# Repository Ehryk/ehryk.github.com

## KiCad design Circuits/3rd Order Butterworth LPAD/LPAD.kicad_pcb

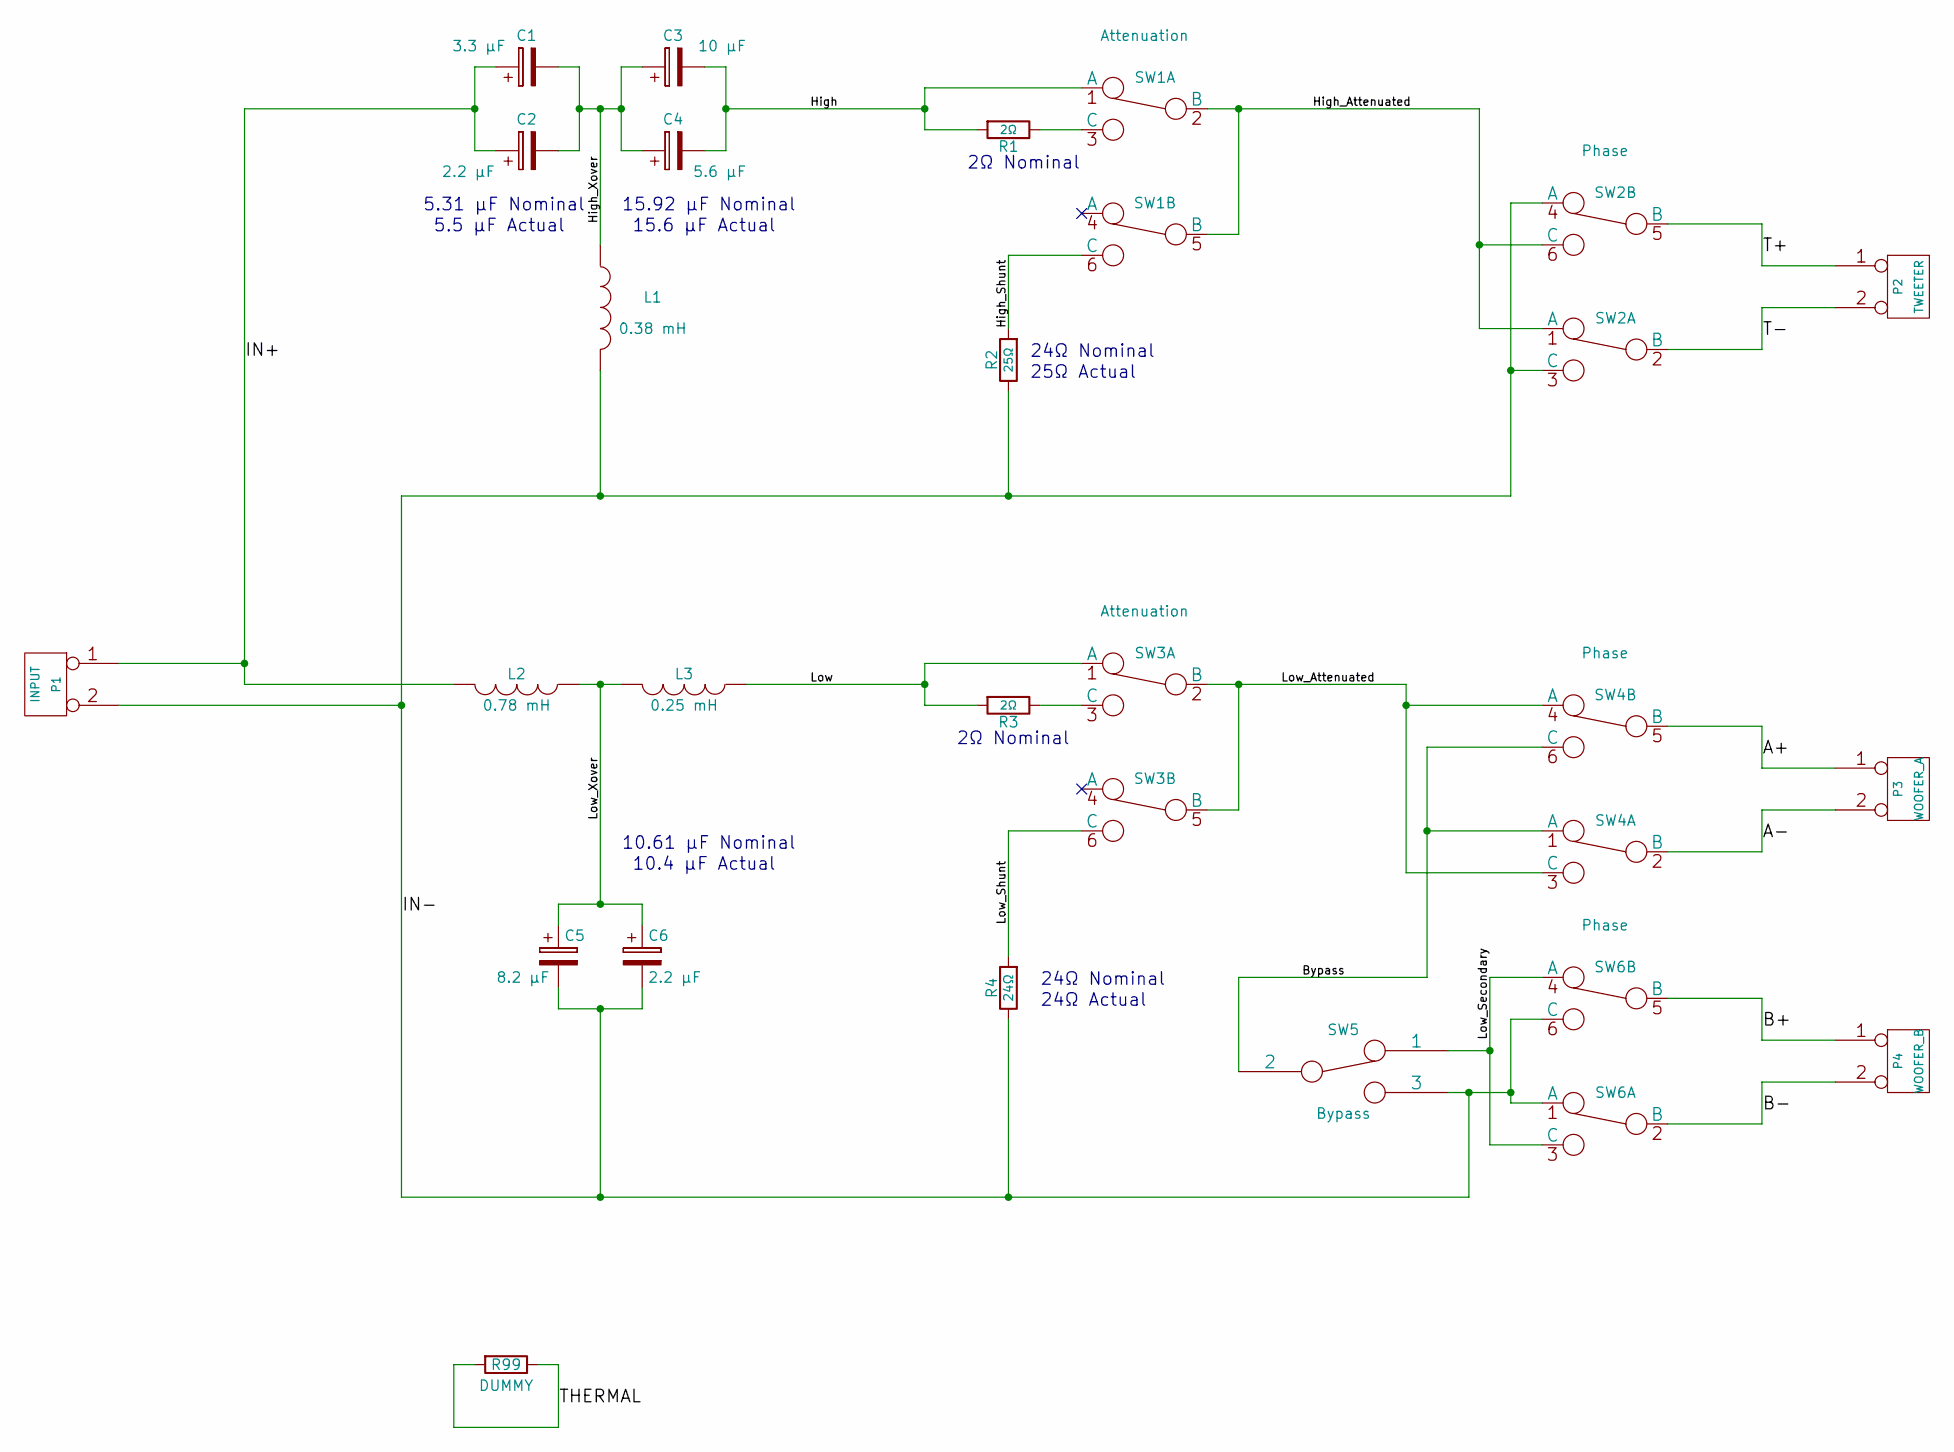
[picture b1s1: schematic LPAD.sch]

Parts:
C1: 3.3 μF; C_AXIAL_15x36
C2, C6: 2.2 μF; C_AXIAL_15x24
C3: 10 μF; C_AXIAL_25x36
C4: 5.6 μF; C_AXIAL_19x36
C5: 8.2 μF; C_AXIAL_23x36
L1: 0.38 mH; ED110-2
L2: 0.78 mH; ED110-2
L3: 0.25 mH; ED110-2
P1: INPUT; ED110-2
P2: TWEETER; ED110-2
P3: WOOFER_A; ED110-2
P4: WOOFER_B; ED110-2
R1: 2Ω; R_WIREWOUND_25W
R2: 25Ω; R_WIREWOUND_25W
R3: 2Ω; R_WIREWOUND_100W
R4: 24Ω; R_WIREWOUND_100W
R99: DUMMY
SW1, SW3: Attenuation; SW_DPDT_RED
SW2, SW4, SW6: Phase; SW_DPDT_RED
SW5: Bypass; SW_SPDT_RED

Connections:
/A+: P3.1, SW4.5 (B)
/A-: P3.2 (PM), SW4.2 (B)
/B+: P4.1, SW6.5 (B)
/B-: P4.2 (PM), SW6.2 (B)
/Bypass: SW4.1 (A), SW4.6 (C), SW5.2
/High: C3.2, C4.2, R1.2, SW1.1 (A)
/High_Attenuated: SW1.2 (B), SW1.5 (B), SW2.1 (A), SW2.6 (C)
/High_Shunt: R2.2, SW1.6 (C)
/High_Xover: C1.2, C2.2, C3.1, C4.1, L1.1
/IN+: C1.1, C2.1, L2.2, P1.1
/IN-: C5.2, C6.2, L1.2, P1.2 (PM), R2.1, R4.1, SW2.3 (C), SW2.4 (A), SW5.3, SW6.1 (A), SW6.6 (C)
/Low: L3.1, R3.2, SW3.1 (A)
/Low_Attenuated: SW3.2 (B), SW3.5 (B), SW4.3 (C), SW4.4 (A)
/Low_Secondary: SW5.1, SW6.3 (C), SW6.4 (A)
/Low_Shunt: R4.2, SW3.6 (C)
/Low_Xover: C5.1, C6.1, L2.1, L3.2
/T+: P2.1, SW2.5 (B)
/T-: P2.2 (PM), SW2.2 (B)
unnamed: R1.1, SW1.3 (C)
unnamed: R3.1, SW3.3 (C)
unnamed: R99.1, R99.2

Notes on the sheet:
10.61 μF Nominal
5.31 μF Nominal
15.92 μF Nominal
10.4 μF Actual
5.5 μF Actual
15.6 μF Actual
24Ω Nominal
24Ω Actual
25Ω Actual
2Ω Nominal

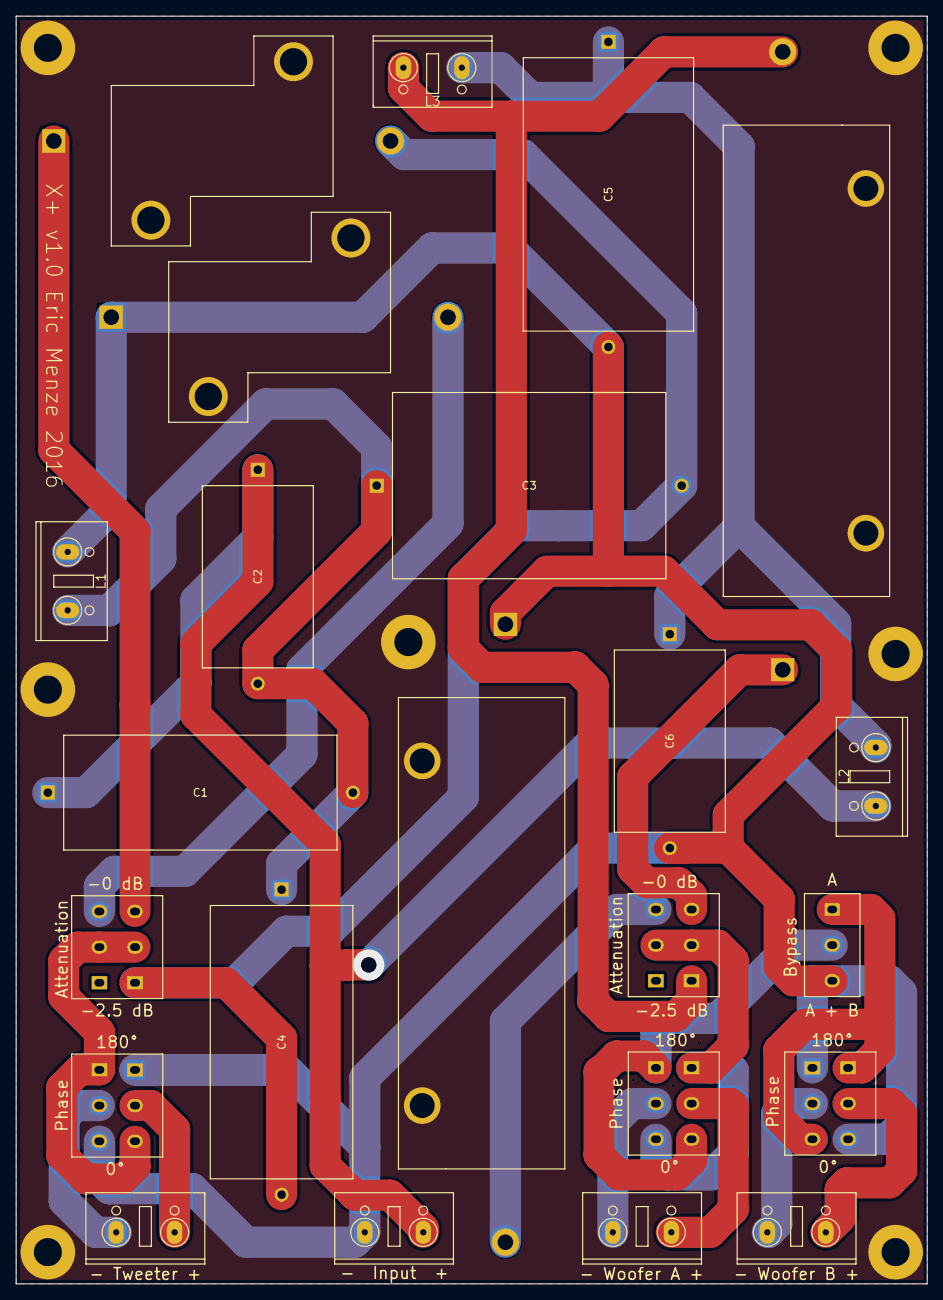
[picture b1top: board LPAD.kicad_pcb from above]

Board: 2 copper layers, 116.8 x 162.6 mm, 30 parts (0 on the bottom side), 20 nets.

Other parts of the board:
S1, S2, S3, S4, S5, S6, S7: #6; 6-32UNC_Screw_Hole

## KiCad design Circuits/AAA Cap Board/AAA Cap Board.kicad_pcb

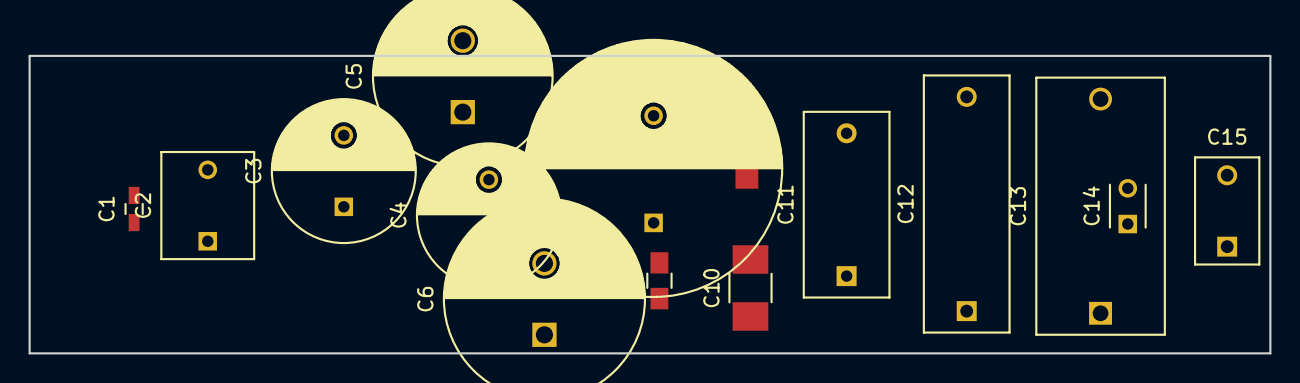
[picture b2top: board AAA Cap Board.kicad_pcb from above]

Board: 2 copper layers, 86.9 x 20.8 mm, 15 parts (0 on the bottom side), 2 nets, no tracks yet.

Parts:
C1: C; C_0603_HandSoldering
C2: CP; C_Rect_L7.5_W6.5_P5
C3: CP1; C_Radial_D10_L13_P5
C4: CP1; C_Radial_D10_L16_P5
C5: CP1; C_Radial_D12.5_L25_P5
C6: CP1; C_Radial_D14_L25_P5
C7: CP1; C_Radial_D18_L36_P7.5
C8: C; C_0805_HandSoldering
C9: C; C_1206_HandSoldering
C10: C; C_1210_HandSoldering
C11: CP; C_Rect_L13_W6_H12_P10
C12: CP; C_Rect_L18_W6_H12_P15
C13: CP; C_Rect_L18_W9_H15_P15
C14: C; C_Disc_D3_P2.5
C15: C; C_Disc_D7.5_P5

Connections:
unnamed: C1.1, C2.1, C3.1, C4.1, C5.1, C6.1, C7.1, C8.1, C9.1, C10.1, C11.1, C12.1, C13.1, C14.1, C15.1
unnamed: C1.2, C2.2, C3.2, C4.2, C5.2, C6.2, C7.2, C8.2, C9.2, C10.2, C11.2, C12.2, C13.2, C14.2, C15.2

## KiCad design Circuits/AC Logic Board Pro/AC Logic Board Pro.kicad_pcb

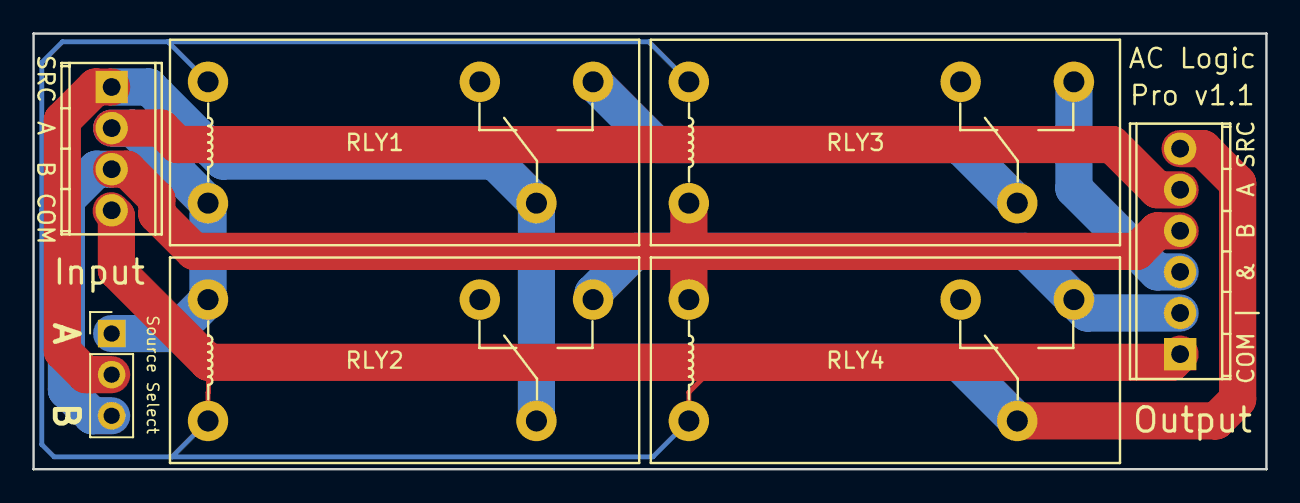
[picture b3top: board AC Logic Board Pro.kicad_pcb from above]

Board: 2 copper layers, 76.2 x 26.9 mm, 7 parts (0 on the bottom side), 7 nets.

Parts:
J1: Input; TerminalBlock_Phoenix_MPT-2.54mm_4pol
J2: Output; TerminalBlock_Phoenix_MPT-2.54mm_6pol
JP1: Source Select; Pin_Header_Straight_1x03_Pitch2.54mm
RLY1: AND_A; TE-RT1-3.5mm
RLY2: OR_A; TE-RT1-3.5mm
RLY3: AND_B; TE-RT1-3.5mm
RLY4: OR_B; TE-RT1-3.5mm

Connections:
A: J1.2, J2.5, JP1.1, RLY1.A2, RLY2.A1
AND: J2.3, RLY3.14
B: J1.3, J2.4, JP1.3, RLY3.A2, RLY4.A1
COMMON: J1.4, J2.1, RLY1.A1, RLY2.A2, RLY3.A1, RLY4.A2
INT_AND: RLY1.14, RLY3.11
OR: J2.2, RLY2.14, RLY4.14
SOURCE: J1.1, J2.6, JP1.2, RLY1.11, RLY2.11, RLY4.11

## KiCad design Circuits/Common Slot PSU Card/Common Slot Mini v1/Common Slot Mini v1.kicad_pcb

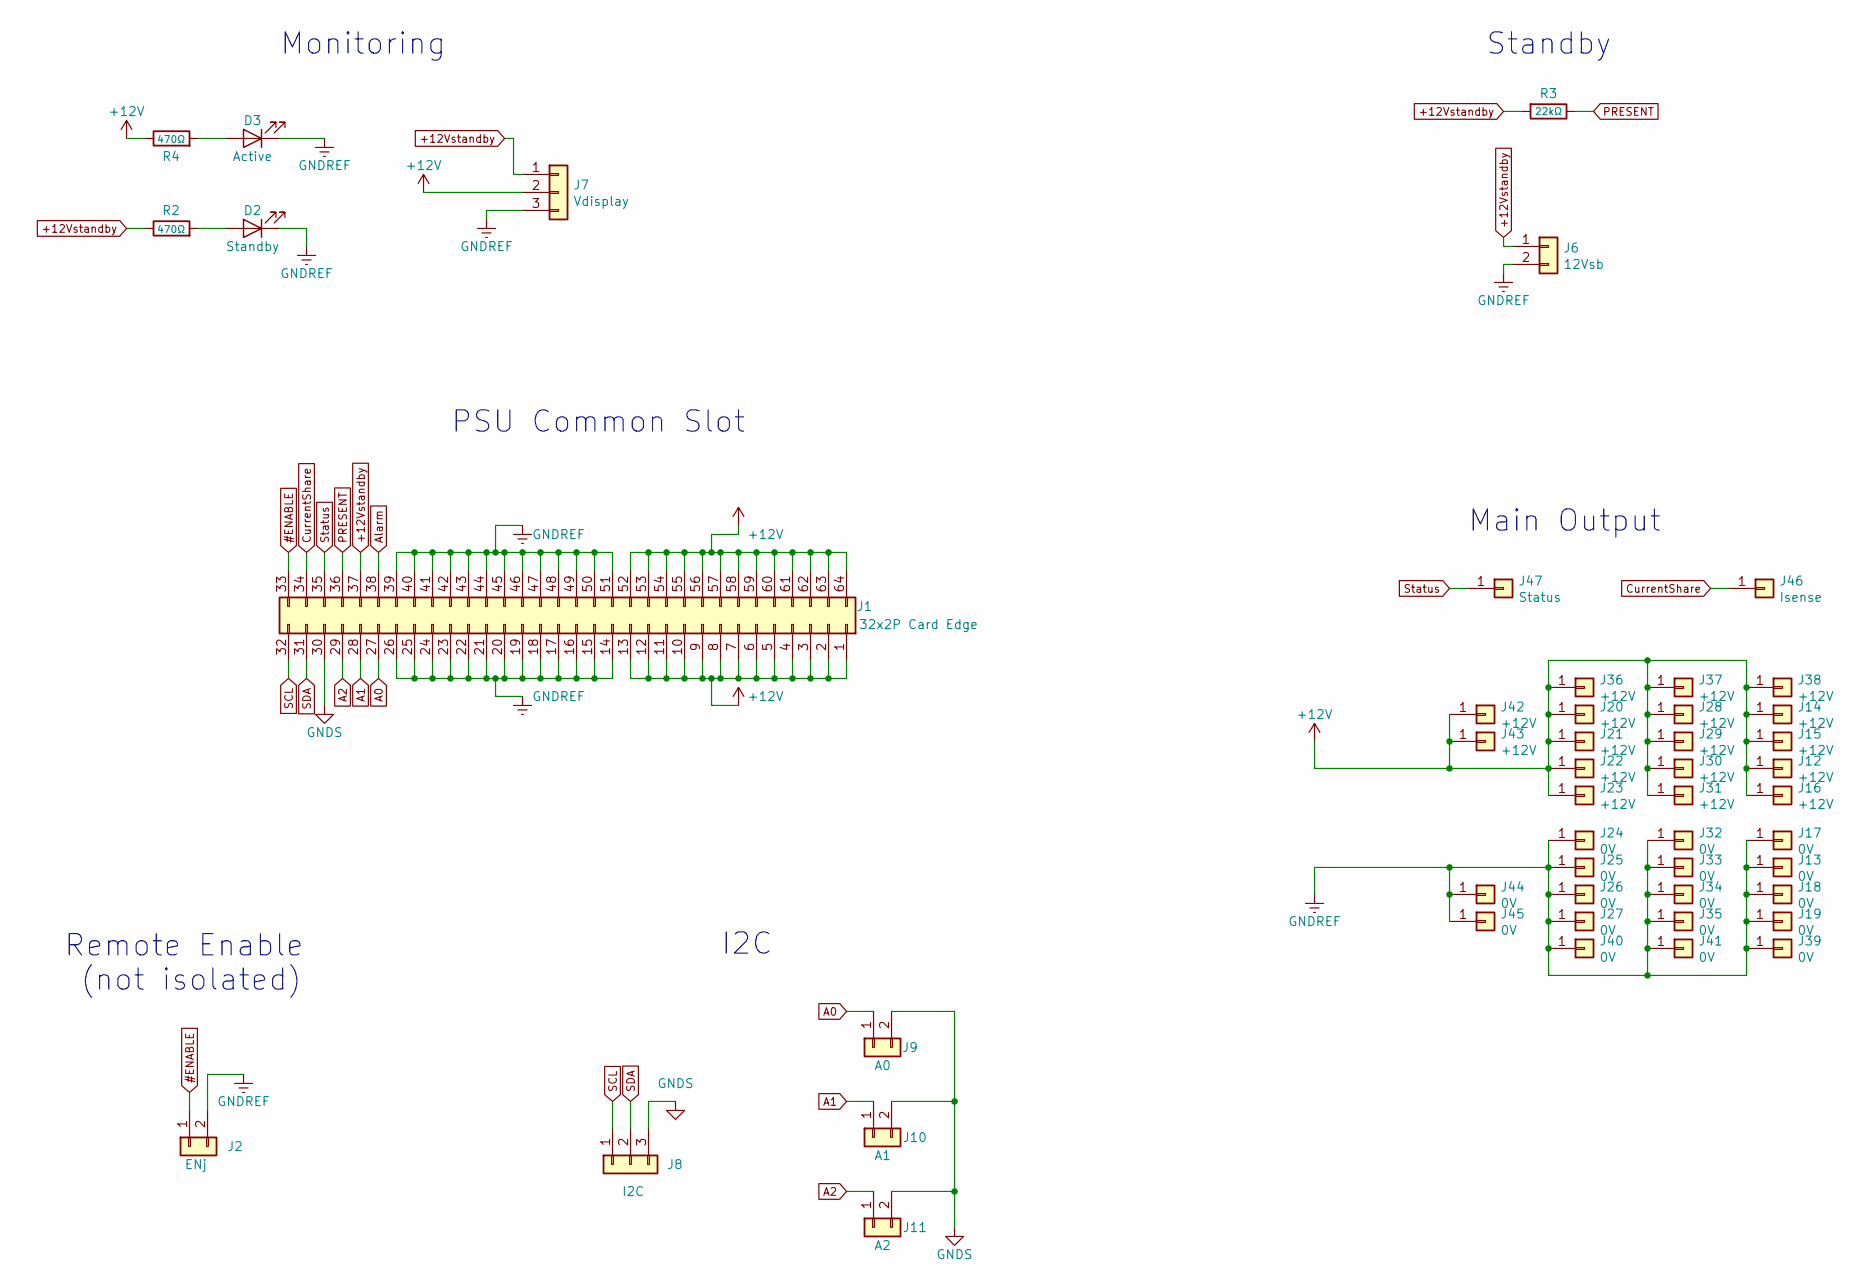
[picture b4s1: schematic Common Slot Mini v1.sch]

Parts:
D2: Standby; LED_1206_HandSoldering
D3: Active; LED_1206_HandSoldering
J1: 32x2P Card Edge; CommonSlot_2x32P_2.54mm
J2: ENj; Pin_Header_Straight_1x02_Pitch2.54mm
J6: 12Vsb; Pin_Header_Straight_1x02_Pitch2.54mm
J7: Vdisplay; Pin_Header_Straight_1x03_Pitch2.54mm
J8: I2C; PinHeader_1x03_P2.54mm_Vertical
J9: A0; SolderJumper-2_P1.3mm_Open_RoundedPad1.0x1.5mm
J10: A1; SolderJumper-2_P1.3mm_Open_RoundedPad1.0x1.5mm
J11: A2; SolderJumper-2_P1.3mm_Open_RoundedPad1.0x1.5mm
J12, J14, J15, J16, J20, J21, J22, J23, J28, J29, J30, J31, J36, J37, J38: +12V; WIRE-12AWG
J13, J17, J18, J19, J24, J25, J26, J27, J32, J33, J34, J35, J39, J40, J41: 0V; WIRE-12AWG
J42, J43: +12V; WIRE-16AWG
J44, J45: 0V; WIRE-16AWG
J46: Isense; WIRE-16AWG
J47: Status; WIRE-20AWG
R2, R4: 470Ω; R_1206_HandSoldering
R3: 22kΩ; R_1206_HandSoldering

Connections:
#ENABLE: J1.33, J2.1
+12V: J1.1, J1.2, J1.3, J1.4, J1.5, J1.6, J1.7, J1.8, J1.9, J1.10, J1.11, J1.12, J1.13, J1.52, J1.53, J1.54, J1.55, J1.56, J1.57, J1.58, J1.59, J1.60, J1.61, J1.62, J1.63, J1.64, J7.2, J12.1, J14.1, J15.1, J16.1, J20.1, J21.1, J22.1, J23.1, J28.1, J29.1, J30.1, J31.1, J36.1, J37.1, J38.1, J42.1, J43.1, R4.1
+12Vstandby: J1.37, J6.1, J7.1, R2.1, R3.2
A0: J1.27, J9.1
A1: J1.28, J10.1
A2: J1.29, J11.1
Alarm: J1.38
CurrentShare: J1.34, J46.1
GNDREF: D2.1 (K), D3.1 (K), J1.14, J1.15, J1.16, J1.17, J1.18, J1.19, J1.20, J1.21, J1.22, J1.23, J1.24, J1.25, J1.26, J1.39, J1.40, J1.41, J1.42, J1.43, J1.44, J1.45, J1.46, J1.47, J1.48, J1.49, J1.50, J1.51, J2.2, J6.2, J7.3, J13.1, J17.1, J18.1, J19.1, J24.1, J25.1, J26.1, J27.1, J32.1, J33.1, J34.1, J35.1, J39.1, J40.1, J41.1, J44.1, J45.1
GNDS: J1.30, J8.3, J9.2, J10.2, J11.2
unnamed: D2.2 (A), R2.2
unnamed: D3.2 (A), R4.2
PRESENT: J1.36, R3.1
SCL: J1.32, J8.1
SDA: J1.31, J8.2
Status: J1.35, J47.1

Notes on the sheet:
Remote Enable (not isolated)
Main Output
Standby
I2C
PSU Common Slot
Monitoring

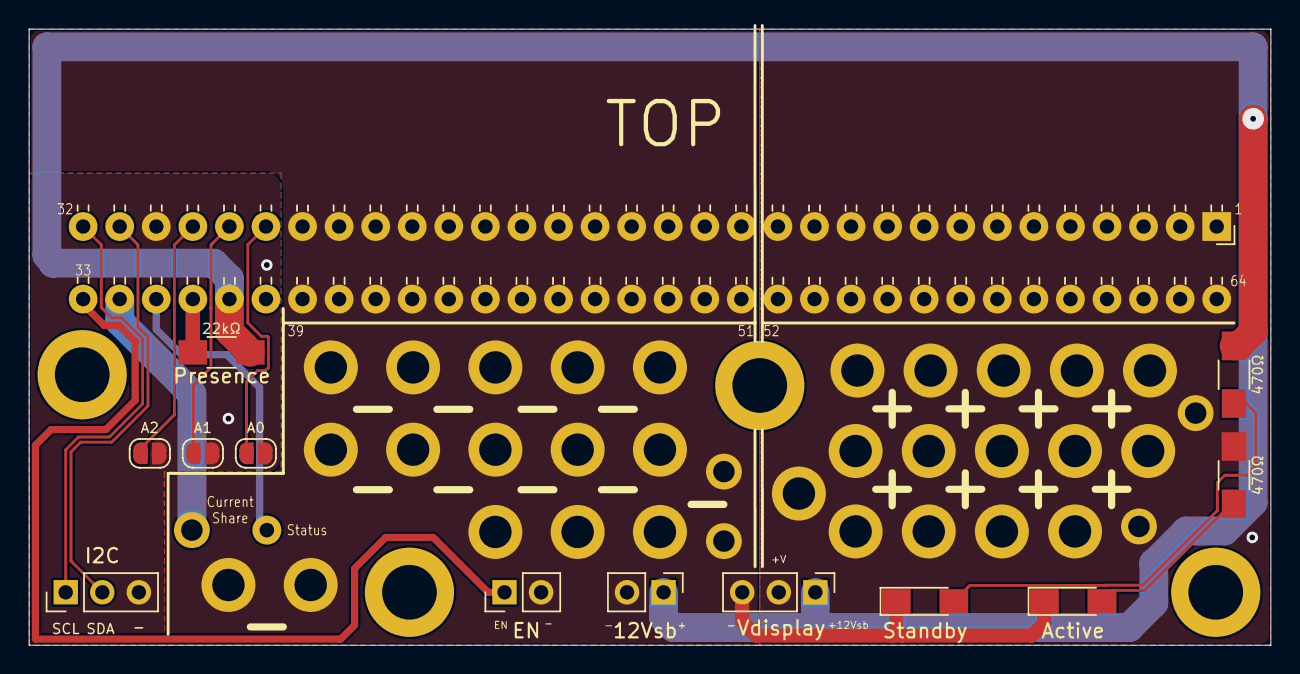
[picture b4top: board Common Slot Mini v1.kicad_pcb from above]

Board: 2 copper layers, 86.2 x 42.8 mm, 53 parts (0 on the bottom side), 15 nets.

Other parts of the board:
Ref**: Val**; M3_Screw_Hole
Ref**#2, Ref**#3, Ref**#4: Val**; M3_Screw_Hole

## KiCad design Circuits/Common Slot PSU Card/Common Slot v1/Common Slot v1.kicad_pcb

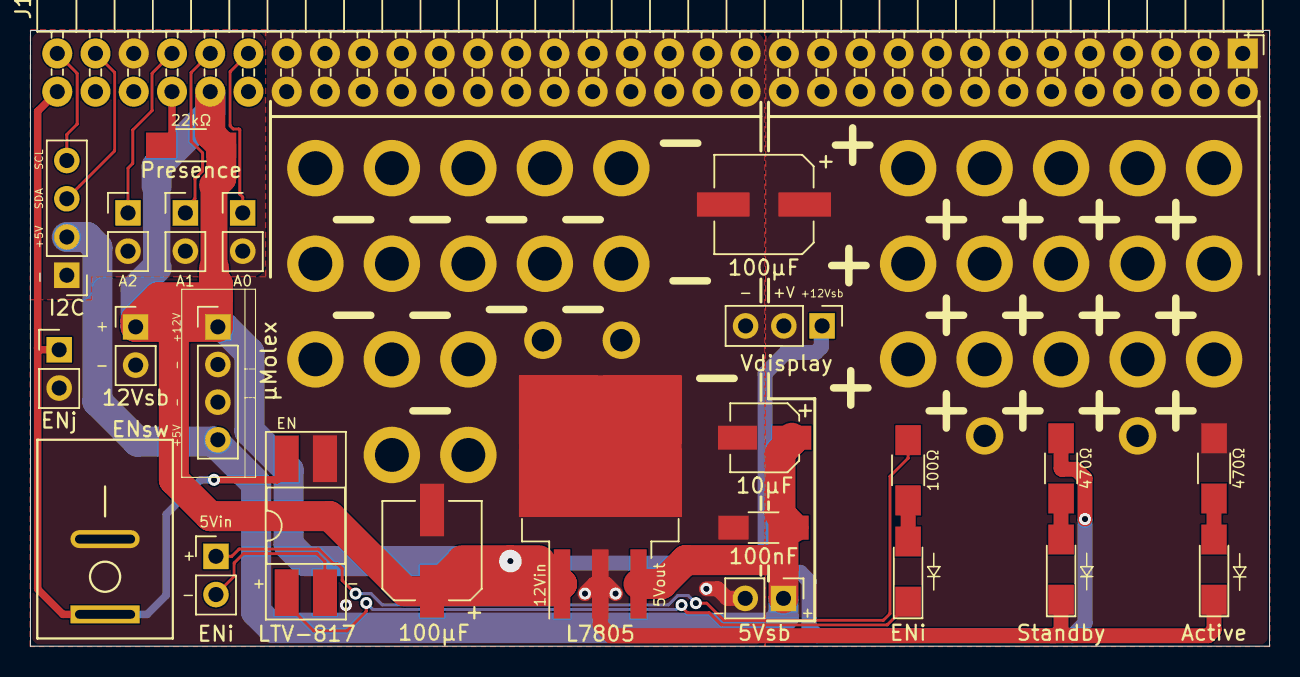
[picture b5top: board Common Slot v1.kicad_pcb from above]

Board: 2 copper layers, 82.3 x 40.9 mm, 59 parts (0 on the bottom side), 18 nets.

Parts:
C1, C4: 100µF; CP_Elec_6.3x5.3
C2: 10µF; CP_Elec_4x5.3
C3: 100nF; C_1206_HandSoldering
D1: ENi; LED_1206_HandSoldering
D2: Standby; LED_1206_HandSoldering
D3: Active; LED_1206_HandSoldering
J1: 32x2P Card Edge; CommonSlot_2x32P_2.54mm
J2: ENj; Pin_Header_Straight_1x02_Pitch2.54mm
J3: ENi; Pin_Header_Straight_1x02_Pitch2.54mm
J4: µMolex; Berg_FDD_Power_1x04_2.50mm
J5: 5Vsb; Pin_Header_Straight_1x02_Pitch2.54mm
J6: 12Vsb; Pin_Header_Straight_1x02_Pitch2.54mm
J7: Vdisplay; Pin_Header_Straight_1x03_Pitch2.54mm
J8: I2C; Pin_Header_Straight_1x04_Pitch2.54mm
J9: A0; Pin_Header_Straight_1x02_Pitch2.54mm
J10: A1; Pin_Header_Straight_1x02_Pitch2.54mm
J11: A2; Pin_Header_Straight_1x02_Pitch2.54mm
J12, J14, J15, J16, J20, J21, J22, J23, J28, J29, J30, J31, J36, J37, J38: +12V; WIRE-12AWG
J13, J17, J18, J19, J24, J25, J26, J27, J32, J33, J34, J35, J39, J40, J41: 0V; WIRE-12AWG
J42, J43: +12V; WIRE-16AWG
J44, J45: 0V; WIRE-16AWG
R1: 100Ω; R_1206_HandSoldering
R2, R4: 470Ω; R_1206_HandSoldering
R3: 22kΩ; R_1206_HandSoldering
SW1: ENsw; SW_SPST_Rocker
U1: LTV-817; DIP-4_W8.89mm_SMDSocket_LongPads
U2: L7805; TO-263-3_TabPin2

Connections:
#ENABLE: J1.33, J2.1, SW1.1, U1.4
+5V: C2.1, C3.1, J4.4, J5.1, J8.2, U2.3
+12V: C4.1, J1.1, J1.2, J1.3, J1.4, J1.5, J1.6, J1.7, J1.8, J1.9, J1.10, J1.11, J1.12, J1.13, J1.52, J1.53, J1.54, J1.55, J1.56, J1.57, J1.58, J1.59, J1.60, J1.61, J1.62, J1.63, J1.64, J7.2, J12.1, J14.1, J15.1, J16.1, J20.1, J21.1, J22.1, J23.1, J28.1, J29.1, J30.1, J31.1, J36.1, J37.1, J38.1, J42.1, J43.1, R4.1
+12Vstandby: C1.1, J1.37, J4.1, J6.1, J7.1, R2.1, R3.2, U2.1
A0: J1.27, J9.1
A1: J1.28, J10.1
A2: J1.29, J11.1
GNDREF: C1.2, C2.2, C3.2, C4.2, D2.1, D3.1, J1.14, J1.15, J1.16, J1.17, J1.18, J1.19, J1.20, J1.21, J1.22, J1.23, J1.24, J1.25, J1.26, J1.39, J1.40, J1.41, J1.42, J1.43, J1.44, J1.45, J1.46, J1.47, J1.48, J1.49, J1.50, J1.51, J2.2, J4.2, J4.3, J5.2, J6.2, J7.3, J13.1, J17.1, J18.1, J19.1, J24.1, J25.1, J26.1, J27.1, J32.1, J33.1, J34.1, J35.1, J39.1, J40.1, J41.1, J44.1, J45.1, SW1.2, U1.3, U2.2
GNDS: J1.30, J8.1, J9.2, J10.2, J11.2
unnamed: D1.1, U1.1
unnamed: D1.2, R1.1
unnamed: D2.2, R2.2
unnamed: D3.2, R4.2
unnamed: J3.1, R1.2
unnamed: J3.2, U1.2
PRESENT: J1.36, R3.1
SCL: J1.32, J8.4
SDA: J1.31, J8.3

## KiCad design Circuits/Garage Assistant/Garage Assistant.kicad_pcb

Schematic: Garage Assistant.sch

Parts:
C1, C2: 10µF; C_Radial_D5_L6_P2.5
C3: 100µF; CP_Radial_D6.3mm_P2.50mm
D1, D2, D3, D4: 1N4148; Diode_DO-35_SOD27_Horizontal_RM10
D5: LED_PWR; LED_D5.0mm
D6, D7: 1N4007; Diode_DO-41_SOD81_Horizontal_RM10
D8: LED_OPT; LED_D3.0mm
D9: A; LED-3MM
D10: B; LED-3MM
JP1: CROSSFEED_A; Socket_Strip_Straight_1x03
JP2: CROSSFEED_B; Socket_Strip_Straight_1x03
P1: MOTION_A; Socket_Strip_Straight_1x03
P2: MOTION_B; Socket_Strip_Straight_1x03
P3: AC_IN; bornier2
P4: 3.5mm_11pin; 3.5mm_11PIN
P5: OUT_A; bornier3
P6: OUT_B; bornier3
Q1, Q2: TIP102; TO-220
R1: 47Ω; Resistor_Horizontal_RM7mm
R2, R3: 10kΩ; Resistor_Horizontal_RM7mm
R4, R7, R8, R9: 220Ω; Resistor_Horizontal_RM7mm
R5, R6: 1kΩ; Resistor_Horizontal_RM10mm
RLY1, RLY2: RELAY; Relay
U1: HiLink_5V3W
UC1: Blend_Micro_v1.0

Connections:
120VAC_A: JP1.1, JP2.1, P3.2 (PM), U1.1 (AC)
120VAC_B: JP1.3, JP2.3, P3.1, U1.2 (AC)
+3V3: P4.6 (A_NC), R2.1, UC1.16 (3V3)
+5V: C1.1, C3.1, D6.1 (K), D7.1 (K), P1.3, P2.3, RLY1.2, RLY2.2, U1.4 (DC+), UC1.12 (VIN); also elsewhere on the board
/A_COMMON: JP1.2, P5.1, RLY1.3
/A_NC: P5.2 (PM), RLY1.5
/A_NO: P5.3, RLY1.4
/B_COMMON: JP2.2, P6.1, RLY2.3
/B_NC: P6.2 (PM), RLY2.5
/B_NO: P6.3, RLY2.4
A_LED: R8.2, UC1.28 (D9/PWM); also elsewhere on the board
A_MOTION: P1.2 (PM), UC1.20 (A3); also elsewhere on the board
A_RELAY: R5.2, UC1.27 (D10/PWM/A10); also elsewhere on the board
BIAS: C2.1, D2.2 (A), D4.1 (K), P4.5 (Tip), R1.2, R2.2, R3.1, UC1.22 (A1); also elsewhere on the board
B_MOTION: P2.2 (PM), UC1.19 (A4); also elsewhere on the board
B_RELAY: R6.2, UC1.25 (D12/A11); also elsewhere on the board
CS_CONNECT: P4.7 (A_COM), UC1.21 (A2); also elsewhere on the board
GND: C1.2, C2.2, C3.2, D5.1 (K), D8.1 (K), D9.1 (K), D10.1 (K), P1.1, P2.1, P4.8 (A_NO), Q1.3 (E), Q2.3 (E), R3.2, U1.3 (DC-), UC1.13 (GND), UC1.14 (GND), UC1.15 (GND); also elsewhere on the board
unnamed: D1.2 (A), D2.1 (K)
unnamed: D3.1 (K), D4.2 (A)
unnamed: D5.2 (A), R4.1
unnamed: D6.2 (A), Q1.2 (C), RLY1.1
unnamed: D7.2 (A), Q2.2 (C), RLY2.1
unnamed: D8.2 (A), R7.1
unnamed: D9.2 (A), R8.1
unnamed: D10.2 (A), R9.1
unnamed: Q1.1 (B), R5.1
unnamed: Q2.1 (B), R6.1
unnamed: R9.2, UC1.26 (D11/PWM)
OPT_LED: R7.2, UC1.24 (D13/PWM/LED)
PWR_LED: R4.2, UC1.2 (D5/PWM); also elsewhere on the board
SENSE: D1.1 (K), D3.2 (A), P4.1 (Sleeve), R1.1, UC1.23 (A0); also elsewhere on the board

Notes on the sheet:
AC Input
DC Rectification
Microcontroller
Output A
Output B
Power LED
Current Sense
Burden Resistor
1N4148 x4
Burden Resistor Values: 3.3V Max 0 - 100A 23Ω 0 - 50A 46Ω 0 - 30A 76Ω 0 - 20A 112Ω 0 - 10A 224Ω
Motion Sense
Optional LED

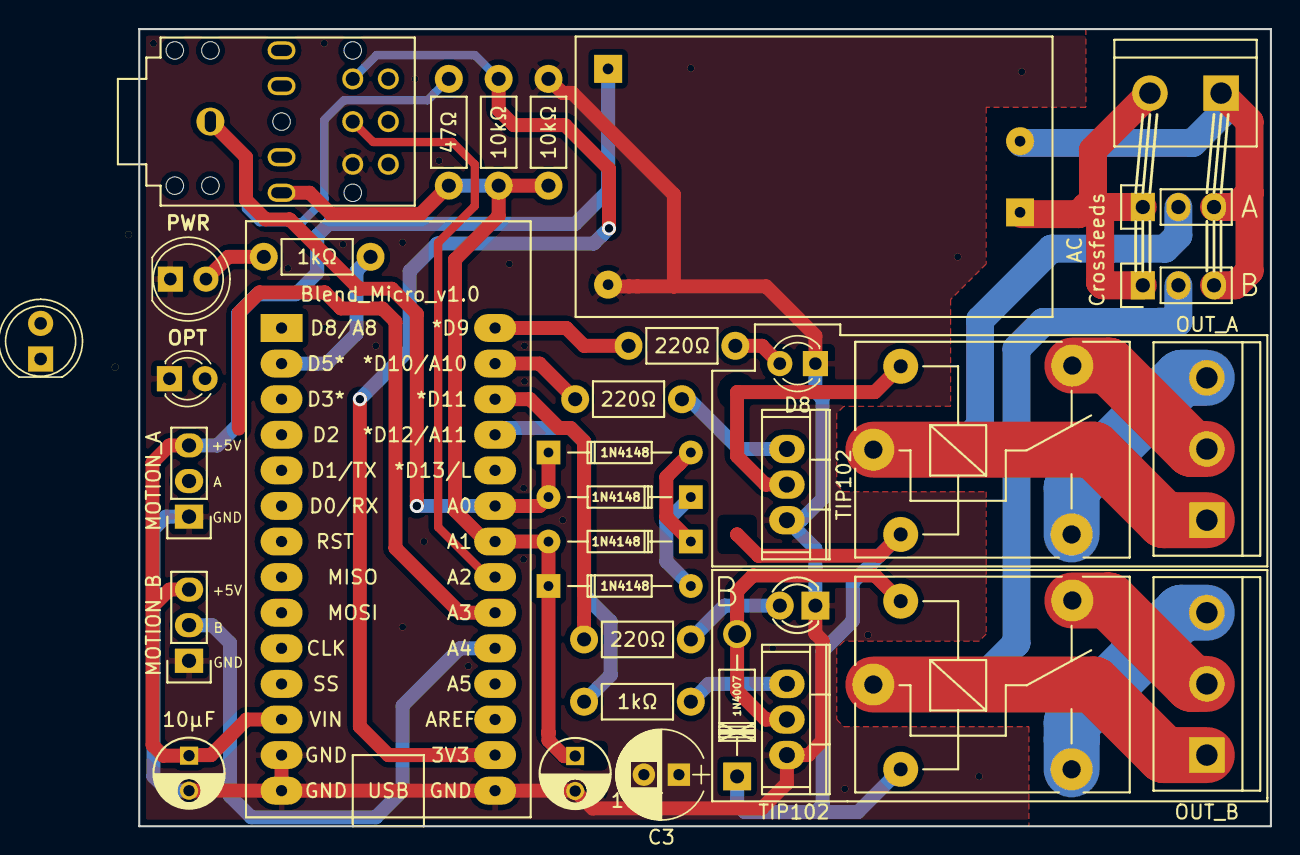
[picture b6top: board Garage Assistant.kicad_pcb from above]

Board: 2 copper layers, 80.8 x 56.9 mm, 35 parts (0 on the bottom side), 29 nets.

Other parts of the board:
MC1: Blend_Micro_v1.0

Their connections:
+5V: MC1.12; also elsewhere on the board
A_LED: MC1.28; also elsewhere on the board
A_MOTION: MC1.20; also elsewhere on the board
A_RELAY: MC1.27; also elsewhere on the board
BIAS: MC1.22; also elsewhere on the board
B_MOTION: MC1.19; also elsewhere on the board
B_RELAY: MC1.25; also elsewhere on the board
CS_CONNECT: MC1.21; also elsewhere on the board
GND: MC1.13, MC1.14, MC1.15; also elsewhere on the board
PWR_LED: MC1.2; also elsewhere on the board
SENSE: MC1.23; also elsewhere on the board
